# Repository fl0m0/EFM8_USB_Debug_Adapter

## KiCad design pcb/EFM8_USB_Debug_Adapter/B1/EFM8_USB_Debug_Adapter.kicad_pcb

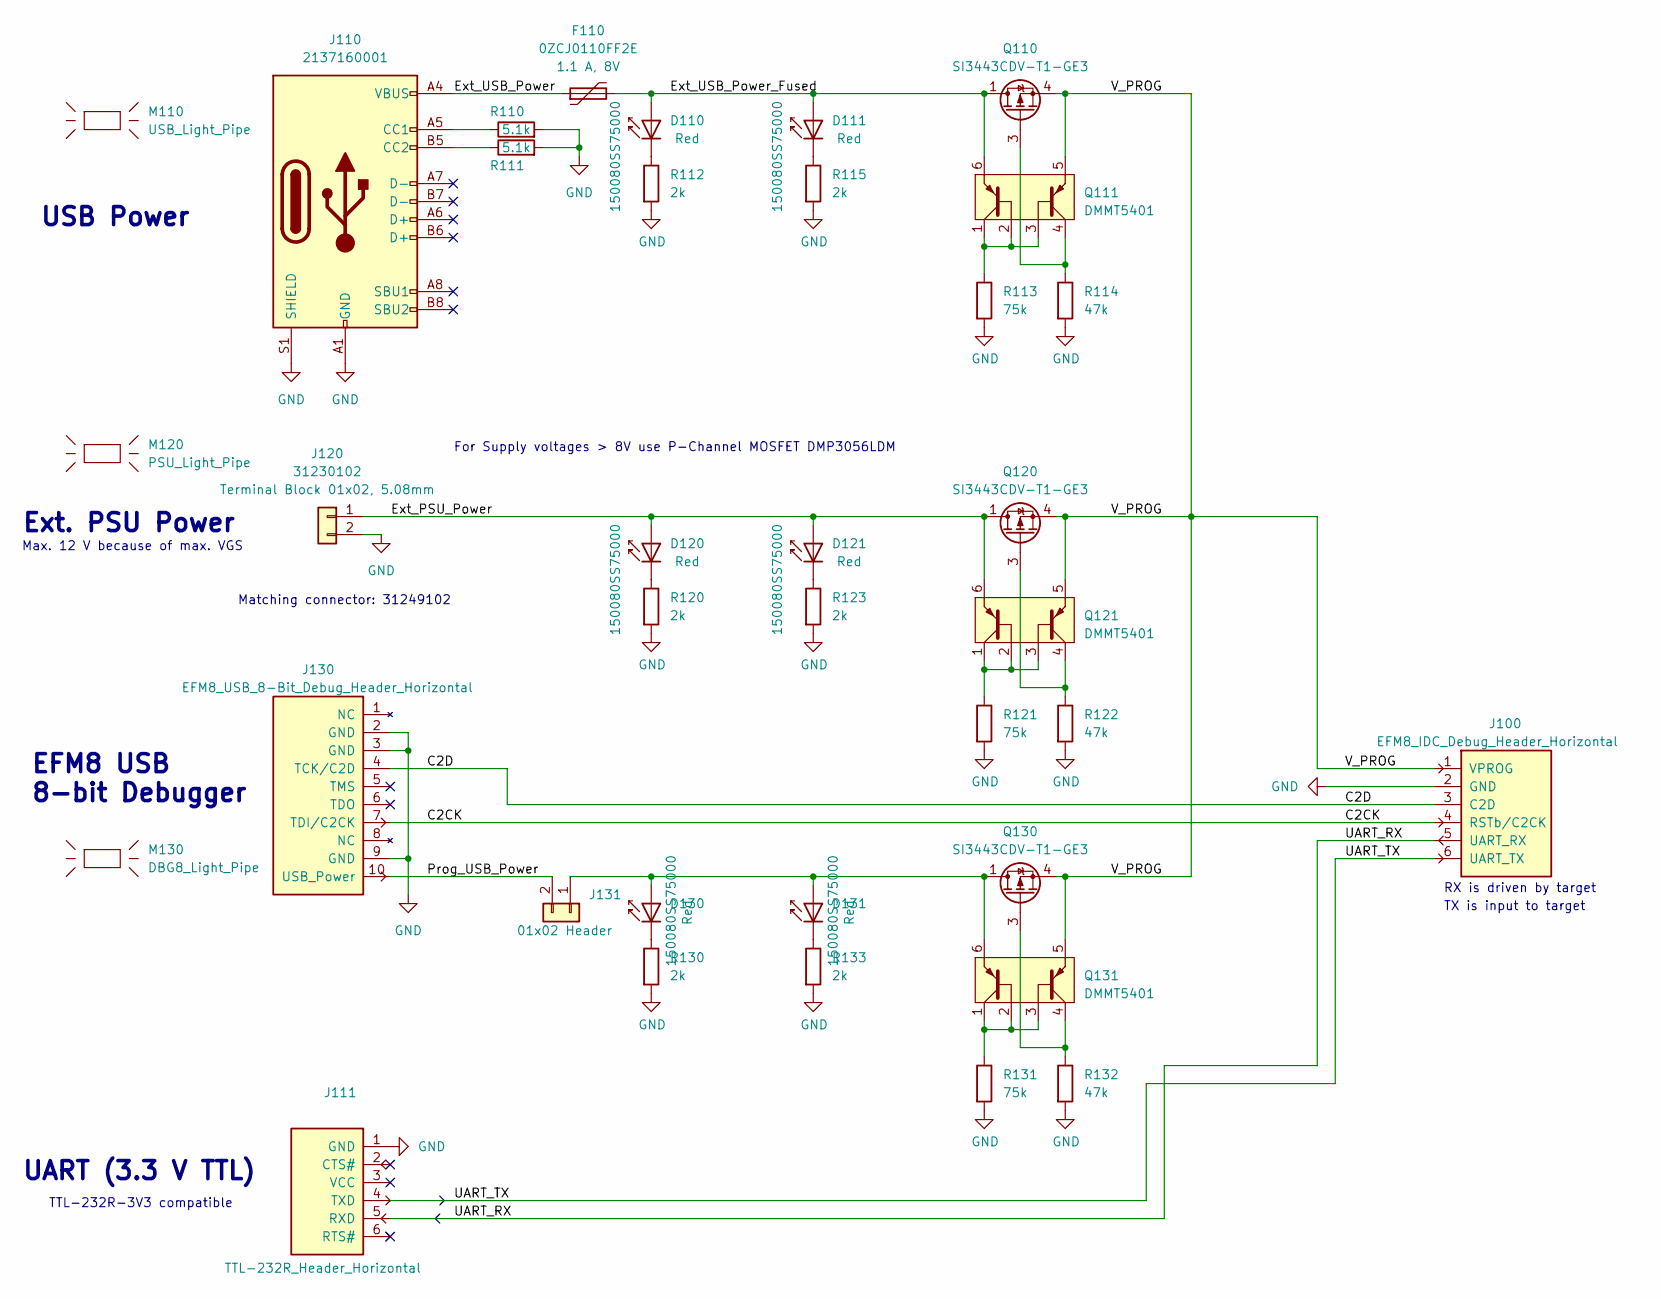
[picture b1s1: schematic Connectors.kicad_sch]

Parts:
D110, D111, D120, D121, D130, D131: 150080SS75000; LED_0805_2012Metric_Pad1.15x1.40mm_HandSolder
F110: 0ZCJ0110FF2E; Fuse_1206_3216Metric_Pad1.42x1.75mm_HandSolder
J100: EFM8_IDC_Debug_Header_Horizontal; IDC-Header_2x03_P2.54mm_Horizontal_61200621721; MPN 61200621721
J110: 2137160001; USB_C_Receptacle_Molex_2137160001
J111: TTL-232R_Header_Horizontal; PinHeader_1x06_P2.54mm_Horizontal; MPN 61300611021
J120: 31230102; PhoenixContact_MSTBA_2,5_2-G-5,08_1x02_P5.08mm_Horizontal; MPN 31230102
J130: EFM8_USB_8-Bit_Debug_Header_Horizontal; IDC-Header_2x05_P2.54mm_Horizontal_61201021721; MPN 61201021721
J131: Header_01x02_Wurth_61300211121; PinHeader_1x02_P2.54mm_Vertical; MPN 61300211121
M110: USB_Light_Pipe; USB_CON_Light_Pipe
M120: PSU_Light_Pipe; PSU_CON_Light_Pipe
M130: DBG8_Light_Pipe; DBG8_CON_Light_Pipe
Q110, Q120, Q130: SI3443CDV-T1-GE3; SOT-23-6_Handsoldering
Q111, Q121, Q131: DMMT5401; SOT-23-6_Handsoldering; MPN DMMT5401-7-F
R110, R111: 5.1k,0603; R_0603_1608Metric_Pad0.98x0.95mm_HandSolder; Tolerance 1%
R112, R115, R120, R123, R130, R133: 2k,0603; R_0603_1608Metric_Pad0.98x0.95mm_HandSolder; Tolerance 1%
R113, R121, R131: 75k,0603; R_0603_1608Metric_Pad0.98x0.95mm_HandSolder; Tolerance 1%
R114, R122, R132: 47k,0603; R_0603_1608Metric_Pad0.98x0.95mm_HandSolder; Tolerance 1%

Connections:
/Connectors/C2CK: J100.4 (RSTb/C2CK), J130.7 (TDI/C2CK)
/Connectors/C2D: J100.3 (C2D), J130.4 (TCK/C2D)
/Connectors/Ext_PSU_Power: D120.2 (A), D121.2 (A), J120.1, Q120.1 (D), Q120.2 (D), Q120.5 (D), Q120.6 (D), Q121.6 (E1)
/Connectors/Ext_USB_Power: F110.1, J110.A4 (VBUS), J110.A9 (VBUS), J110.B4 (VBUS), J110.B9 (VBUS)
/Connectors/Ext_USB_Power_Fused: D110.2 (A), D111.2 (A), F110.2, Q110.1 (D), Q110.2 (D), Q110.5 (D), Q110.6 (D), Q111.6 (E1)
/Connectors/Prog_USB_Power: J130.10 (USB_Power), J131.2
/Connectors/UART_RX: J100.5 (UART_RX), J111.5 (RXD)
/Connectors/UART_TX: J100.6 (UART_TX), J111.4 (TXD)
/Connectors/V_PROG: J100.1 (VPROG), Q110.4 (S), Q111.5 (E2), Q120.4 (S), Q121.5 (E2), Q130.4 (S), Q131.5 (E2)
GND: J100.2 (GND), J110.A1 (GND), J110.A12 (GND), J110.B1 (GND), J110.B12 (GND), J110.S1 (SHIELD), J111.1 (GND), J120.2, J130.2 (GND), J130.3 (GND), J130.9 (GND), R110.2, R111.2, R112.2, R113.2, R114.2, R115.2, R120.2, R121.2, R122.2, R123.2, R130.2, R131.2, R132.2, R133.2
unnamed: D110.1 (K), R112.1
unnamed: D111.1 (K), R115.1
unnamed: D120.1 (K), R120.1
unnamed: D121.1 (K), R123.1
unnamed: D130.2 (A), D131.2 (A), J131.1, Q130.1 (D), Q130.2 (D), Q130.5 (D), Q130.6 (D), Q131.6 (E1)
unnamed: D130.1 (K), R130.1
unnamed: D131.1 (K), R133.1
unnamed: J110.A5 (CC1), R110.1
unnamed: J110.B5 (CC2), R111.1
unnamed: Q110.3 (G), Q111.4 (C2), R114.1
unnamed: Q111.1 (C1), Q111.2 (B1), Q111.3 (B2), R113.1
unnamed: Q120.3 (G), Q121.4 (C2), R122.1
unnamed: Q121.1 (C1), Q121.2 (B1), Q121.3 (B2), R121.1
unnamed: Q130.3 (G), Q131.4 (C2), R132.1
unnamed: Q131.1 (C1), Q131.2 (B1), Q131.3 (B2), R131.1

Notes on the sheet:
TTL-232R-3V3 compatible
Ext. PSU Power
UART (3.3 V TTL)
EFM8 USB 8-bit Debugger
TX is input to target
USB Power
Max. 12 V because of max. VGS
Matching connector: 31249102
RX is driven by target
For Supply voltages > 8V use P-Channel MOSFET DMP3056LDM

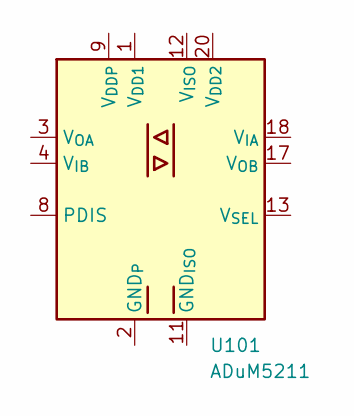
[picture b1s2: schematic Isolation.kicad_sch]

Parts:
U101: ADuM5211; SSOP-20_5.3x7.2mm_P0.65mm

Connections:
unnamed: U101.2 (GND_{P}), U101.5 (GND_{P}), U101.6 (GND_{P}), U101.10 (GND_{P})
unnamed: U101.11 (GND_{ISO}), U101.15 (GND_{ISO}), U101.16 (GND_{ISO}), U101.19 (GND_{ISO})

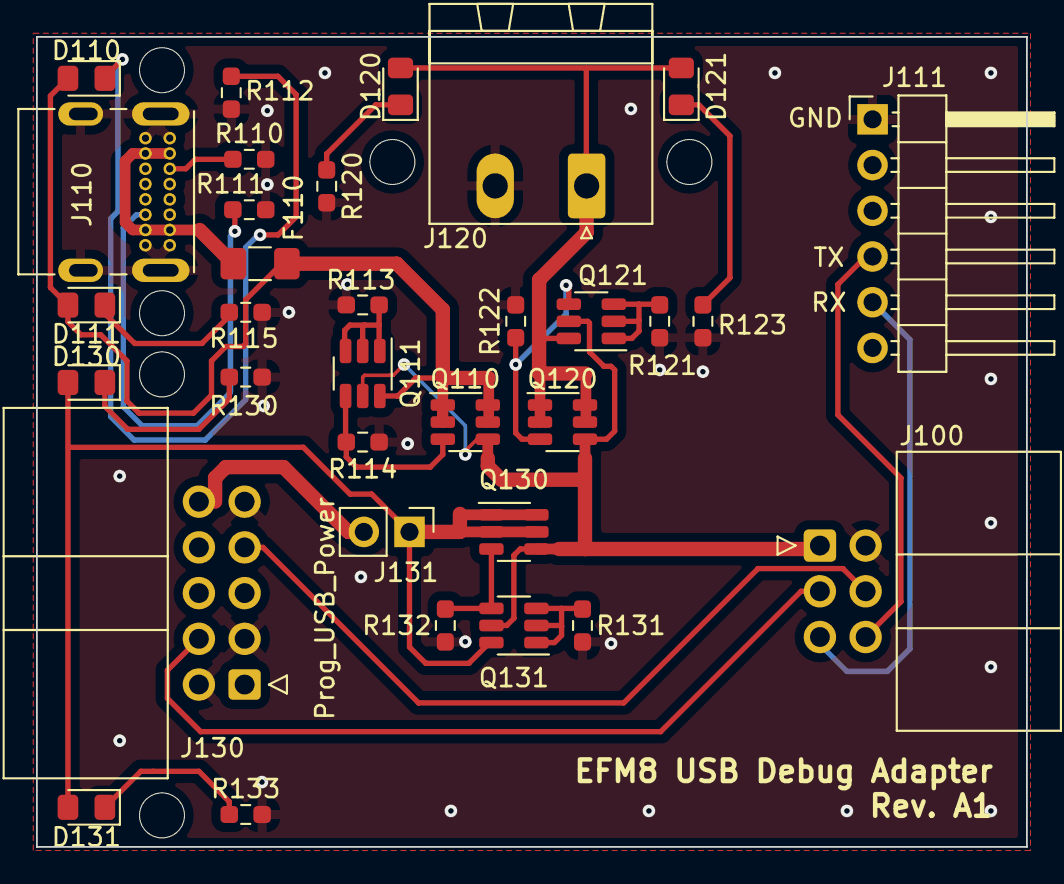
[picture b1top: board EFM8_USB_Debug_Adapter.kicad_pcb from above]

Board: 2 copper layers, 55.0 x 45.0 mm, 36 parts (0 on the bottom side), 25 nets.

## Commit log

2022-10-23 Initialer Commit
2022-10-24 Erstes Layout
2022-10-26 PCB bearbeitet, FreeCAD Projet angelegt
2022-10-28 Mechanik bearbeitet
2022-10-29 Gehäuse bearbeitet
2022-10-31 Light Pipes in KiCad hinzugefügt
2022-10-31 USB Light Pipe bearbeitet
2022-11-03 PSU Stecker Light Pipe bearbeitet
2022-11-05 Lightpipes aktualisiert
2022-11-06 PCB bearbeitet
2022-11-07 Stecker verschoben
2022-11-08 PCB Rev. A1
2022-11-09 Neues Case-Modell
2024-02-17 Update to KiCad 7, add Cura projects
2024-02-17 Add pdf schematic
2024-03-22 Add new revision B1
2024-07-16 Update resistor values, LED colors
